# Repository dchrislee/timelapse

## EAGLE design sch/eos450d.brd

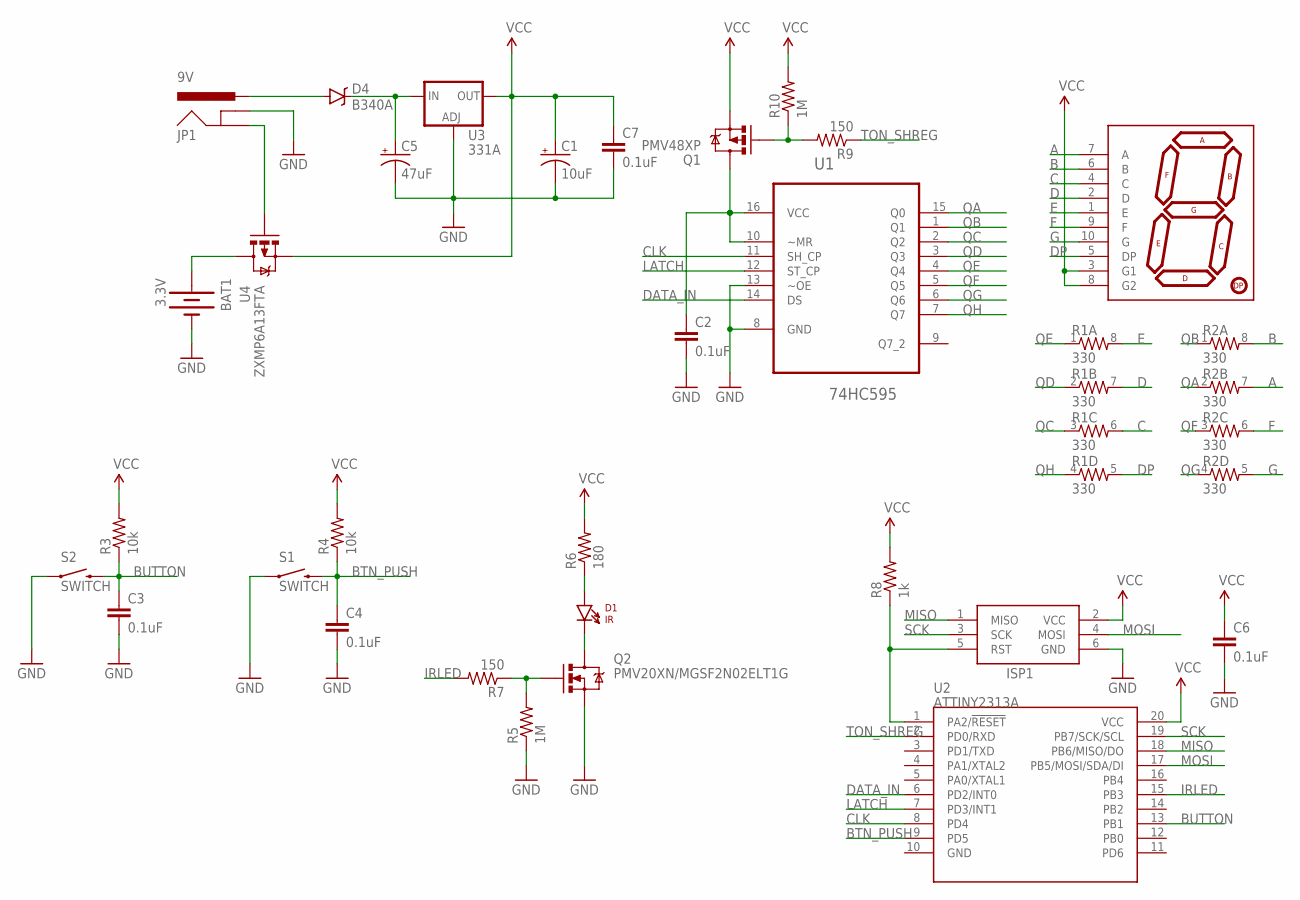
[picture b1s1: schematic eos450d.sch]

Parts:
BAT1: 3.3V; BATTCOM_20MM_PTH
C1: 10uF; EIA3216
C2, C3, C4, C6, C7: 0.1uF; 0603-CAP
C5: 47uF; EIA3528
D1: IR; LTE-302
D2: 7-SEGMENT-DISPLAY-1"-REDEZ; 7-SEGMENT-1"PTH-EZ
D4: B340A; SMA-DIODE
ISP1: AVRISP-6; AVRISP
JP1: 9V; POWER_JACK_SLOT
Q1: PMV48XP; SOT23-3
Q2: PMV20XN/MGSF2N02ELT1G; SOT23-3
R1, R2: 330; 0603-ARV
R3, R4: 10k; 0805
R5, R10: 1M; 0805
R6: 180; 0805
R7, R9: 150; 0805
R8: 1k; 0805
S1, S2: SWITCH; TACTILE-PTH-EZ
U1: 74HC595; SOIC127P600X175-16N
U2: ATTINY2313A; SOP20W
U3: 331A; SOT223
U4: ZXMP6A13FTA; SOT23-3

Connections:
A: D2.7 (A), R2.7 (2)
B: D2.6 (B), R2.8 (2)
BTN_PUSH: C4.1, R4.1, S1.3 (2), U2.9 (PD5)
BUTTON: C3.1, R3.1, S2.3 (2), U2.13 (PB1)
C: D2.4 (C), R1.6 (2)
CLK: U1.11 (SH_CP), U2.8 (PD4)
D: D2.2 (D), R1.7 (2)
DATA_IN: U1.14 (DS), U2.6 (PD2/INT0)
DP: D2.5 (DP), R1.5 (2)
E: D2.1 (E), R1.8 (2)
F: D2.9 (F), R2.6 (2)
G: D2.10 (G), R2.5 (2)
GND: BAT1.2 (-), C1.C (-), C2.2, C3.2, C4.2, C5.C (-), C6.2, C7.2, ISP1.6 (GND), JP1.GND@1 (GNDBREAK), Q2.2 (S), R5.1, S1.1, S2.1, U1.8 (GND), U1.13 (~OE), U3.1 (ADJ)
IRLED: R7.2, U2.15 (PB3)
LATCH: U1.12 (ST_CP), U2.7 (PD3/INT1)
MISO: ISP1.1 (MISO), U2.18 (PB6/MISO/DO)
MOSI: ISP1.4 (MOSI), U2.17 (PB5/MOSI/SDA/DI)
unnamed: D1.A, R6.1
unnamed: Q2.1 (G), R5.2, R7.1
unnamed: D1.C, Q2.3 (D)
unnamed: Q1.1 (G), R9.2, R10.1
unnamed: C2.1, Q1.3 (D), U1.10 (~MR), U1.16 (VCC)
unnamed: C5.A (+), D4.C, U3.3 (IN)
unnamed: ISP1.5 (RST), R8.1, U2.1 (PA2/!RESET)
unnamed: D4.A, JP1.PWR
unnamed: BAT1.1 (+), U4.3 (D)
unnamed: JP1.GND@2 (GND), U4.1 (G)
QA: R2.2 (1), U1.15 (Q0)
QB: R2.1, U1.1 (Q1)
QC: R1.3 (1), U1.2 (Q2)
QD: R1.2 (1), U1.3 (Q3)
QE: R1.1, U1.4 (Q4)
QF: R2.3 (1), U1.5 (Q5)
QG: R2.4 (1), U1.6 (Q6)
QH: R1.4 (1), U1.7 (Q7)
SCK: ISP1.3 (SCK), U2.19 (PB7/SCK/SCL)
TON_SHREG: R9.1, U2.2 (PD0/RXD)
VCC: C1.A (+), C6.1, C7.1, D2.3 (G1), D2.8 (G2), ISP1.2 (VCC), Q1.2 (S), R3.2, R4.2, R6.2, R8.2, R10.2, U2.20 (VCC), U3.2 (OUT), U4.2 (S)

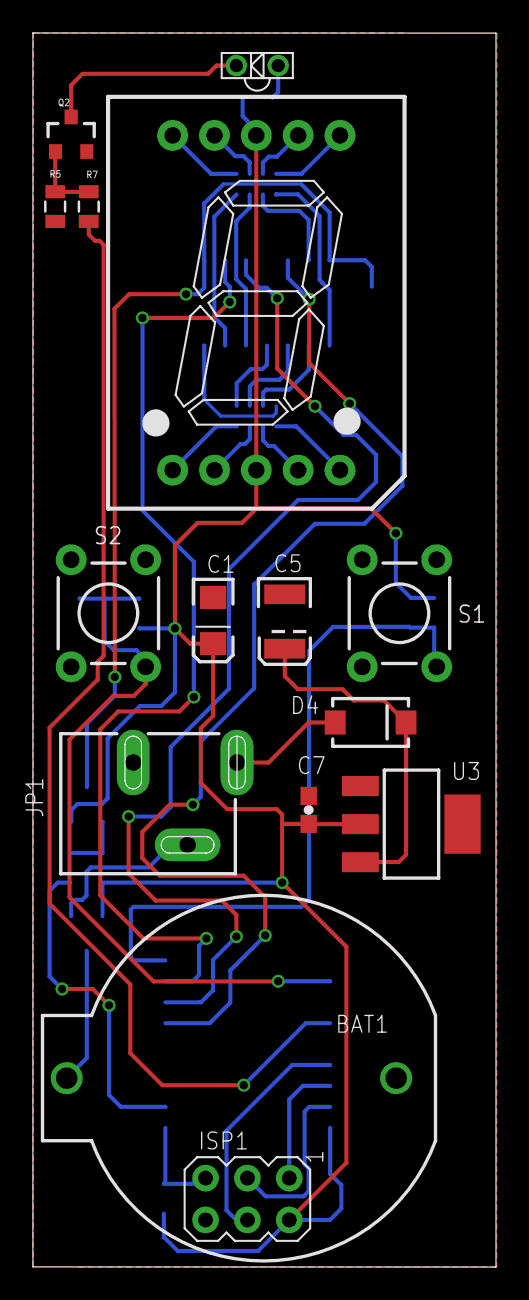
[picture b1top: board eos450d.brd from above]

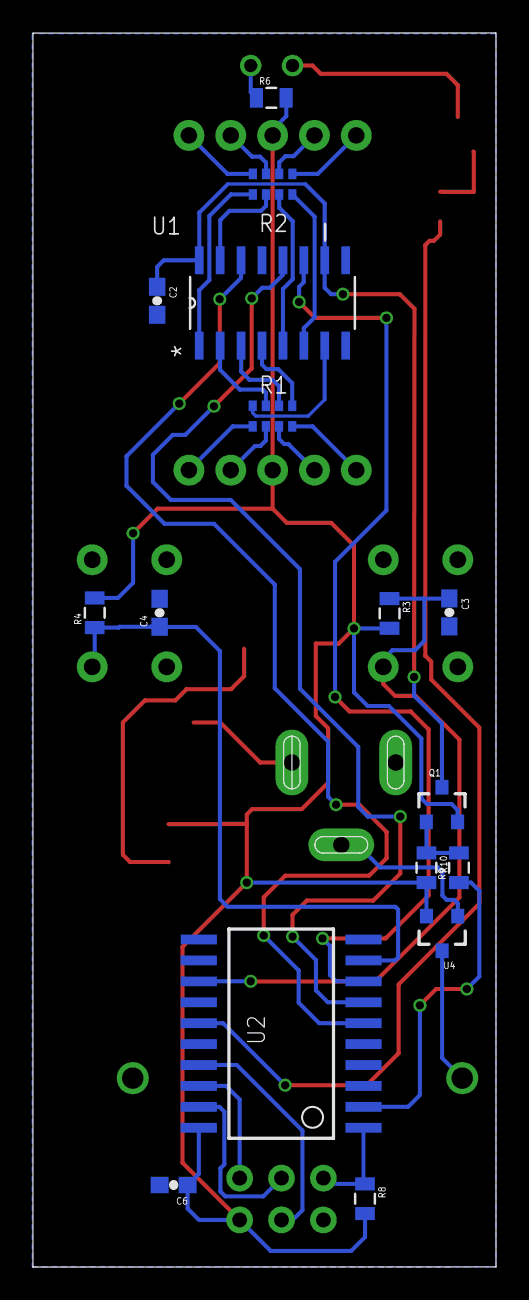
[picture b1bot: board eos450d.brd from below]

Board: 2 copper layers, 28.1 x 74.9 mm, 31 parts (16 on the bottom side), 38 nets.

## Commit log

2014-12-15 Added empty sch
2014-12-24 Added shift register library
2014-12-27 Updated schematic. Updated source code: WDT usage
2015-01-04 Schematic complete. Added Gerber files
2015-01-10 Schematic updated: Auto power switching added
2015-01-10 PDF schematic added
2015-01-24 Changed lifecycle
2015-01-25 Fixed WDT
2015-04-13 Some small changes
2015-04-13 GitIgnore added

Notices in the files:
parts and their libraries:
SparkFun-Electromechanical: Licensing: Creative Commons ShareAlike 4.0 International - https://creativecommons.org/licenses/by-sa/4.0
